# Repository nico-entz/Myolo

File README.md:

# Myolo

Myolo ist ein Partikel/Myonendetektor auf der Basis von Szintillatoren und Silizium-Photodioden, der ohne SMD-Bauteile aufgebaut werden kann.

Myolo nutzt Koinzidenz, um Myonen von anderen Teilchen zu unterscheiden. Um dies zu realisieren, nutzt er zwei voneinander unabhängige Detektoren. Anhand der zeitlichen Korrelation der Signale beider Detektoren kann auf die Teilchenart geschlossen werden.

Als Szintillatoren kommen Bicron BC408-Plastikszintillatoren der Maße 50x50x10 mm zum Einsatz.

Als SiPMs werden onsemi MICROFC-60035-SMT-TR genutzt. Die Bias-Spannung von 29,5 V wird mittels eines simplen DC-DC-Wandlers erzeugt.

Die für die Operationsverstärkerschaltung notwendige symmetrische Versorgungsspannung von +/- 15V wird ebenfalls durch einen DC-DC-Wandler erzeugt.

Myolo basiert lose auf dem CosmicWatch-Projekt (http://www.cosmicwatch.lns.mit.edu/) und nutzt daher auch dessen SiPM-PCB (https://github.com/spenceraxani/CosmicWatch-Desktop-Muon-Detector-v2/blob/master/PCB_Files/PCB_Gerber_files.zip).

Im Gegensatz zu CosmicWatch nutzt Myolo jedoch einen leistungsfähigen STM32H7-Mikrocontroller, wodurch es möglich wird, beide Detektoren quasi zeitgleich auszulesen.

--------------------------------------

Myolo is a particle/muon detector based on scintillators and silicon photodiodes that can be constructed without SMD components.

Myolo uses the coincidence method to distinguish muons from other particles. To achieve this, it uses two independent detectors. The type of particle can be determined based on the temporal correlation of the signals from both detectors.

Bicron BC408 plastic scintillators measuring 50x50x10 mm are used as scintillators.

Onsemi MICROFC-60035-SMT-TR are used as SiPMs. The bias voltage of 29.5 V is generated by a simple DC-DC converter. 

The symmetrical supply voltage of +/- 15V required for the operational amplifier circuit is also generated by a DC-DC converter.

Myolo is loosely based on the CosmicWatch project (http://www.cosmicwatch.lns.mit.edu/) and therefore also uses its SiPM PCB (https://github.com/spenceraxani/CosmicWatch-Desktop-Muon-Detector-v2/blob/master/PCB_Files/PCB_Gerber_files.zip).

Unlike CosmicWatch, however, Myolo uses a powerful STM32H7 microcontroller, which makes it possible to read out both detectors virtually simultaneously.

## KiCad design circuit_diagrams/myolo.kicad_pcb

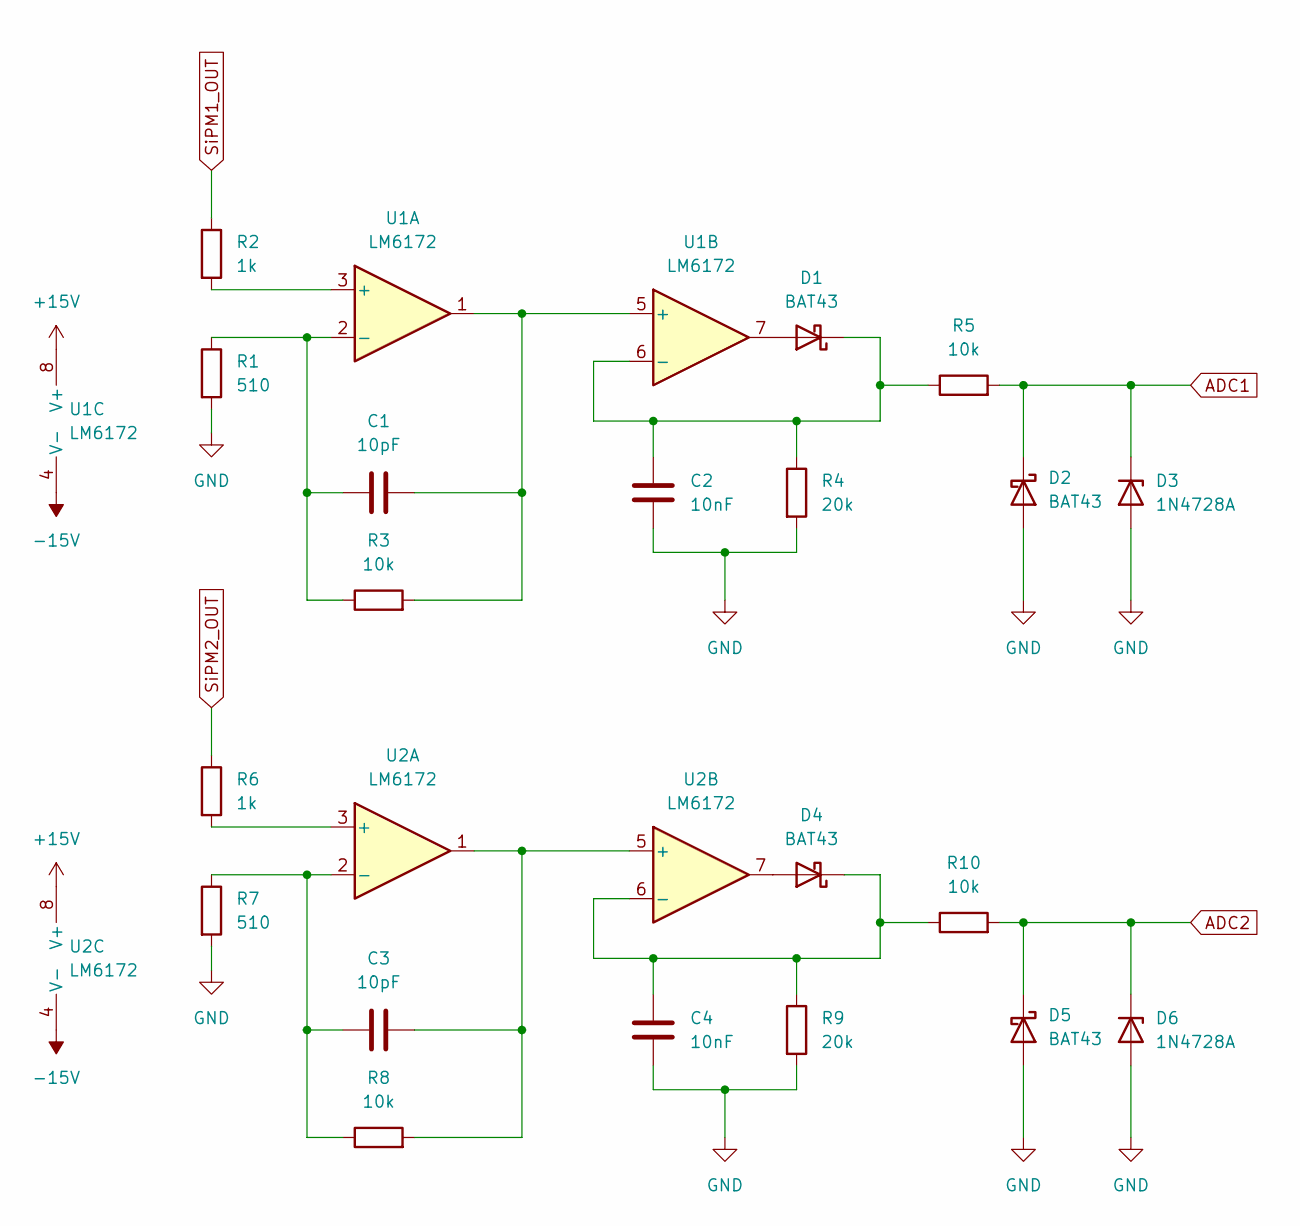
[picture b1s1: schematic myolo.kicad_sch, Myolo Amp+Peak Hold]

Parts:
C1, C3: 10pF; CP_Radial_D4.0mm_P2.00mm
C2, C4: 10nF; CP_Radial_D4.0mm_P2.00mm
D1, D2, D4, D5: BAT43; D_DO-35_SOD27_P7.62mm_Horizontal
D3, D6: 1N4728A; D_DO-41_SOD81_P10.16mm_Horizontal
R1, R7: 510; R_Axial_DIN0207_L6.3mm_D2.5mm_P15.24mm_Horizontal
R2, R6: 1k; R_Axial_DIN0207_L6.3mm_D2.5mm_P15.24mm_Horizontal
R3, R5, R8, R10: 10k; R_Axial_DIN0207_L6.3mm_D2.5mm_P15.24mm_Horizontal
R4, R9: 20k; R_Axial_DIN0207_L6.3mm_D2.5mm_P15.24mm_Horizontal
U1, U2: LM6172; DIP-8_W10.16mm

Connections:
+15V: U1.8 (V+), U2.8 (V+)
-15V: U1.4 (V-), U2.4 (V-)
ADC1: D2.1 (K), D3.1 (K), R5.2
ADC2: D5.1 (K), D6.1 (K), R10.2
GND: C2.2, C4.2, D2.2 (A), D3.2 (A), D5.2 (A), D6.2 (A), R1.2, R4.2, R7.2, R9.2
unnamed: D1.2 (A), U1.7
unnamed: C2.1, D1.1 (K), R4.1, R5.1, U1.6 (-)
unnamed: D4.2 (A), U2.7
unnamed: C4.1, D4.1 (K), R9.1, R10.1, U2.6 (-)
unnamed: R2.2, U1.3 (+)
unnamed: C1.1, R1.1, R3.1, U1.2 (-)
unnamed: C1.2, R3.2, U1.1, U1.5 (+)
unnamed: R6.2, U2.3 (+)
unnamed: C3.1, R7.1, R8.1, U2.2 (-)
unnamed: C3.2, R8.2, U2.1, U2.5 (+)
SiPM1_OUT: R2.1
SiPM2_OUT: R6.1

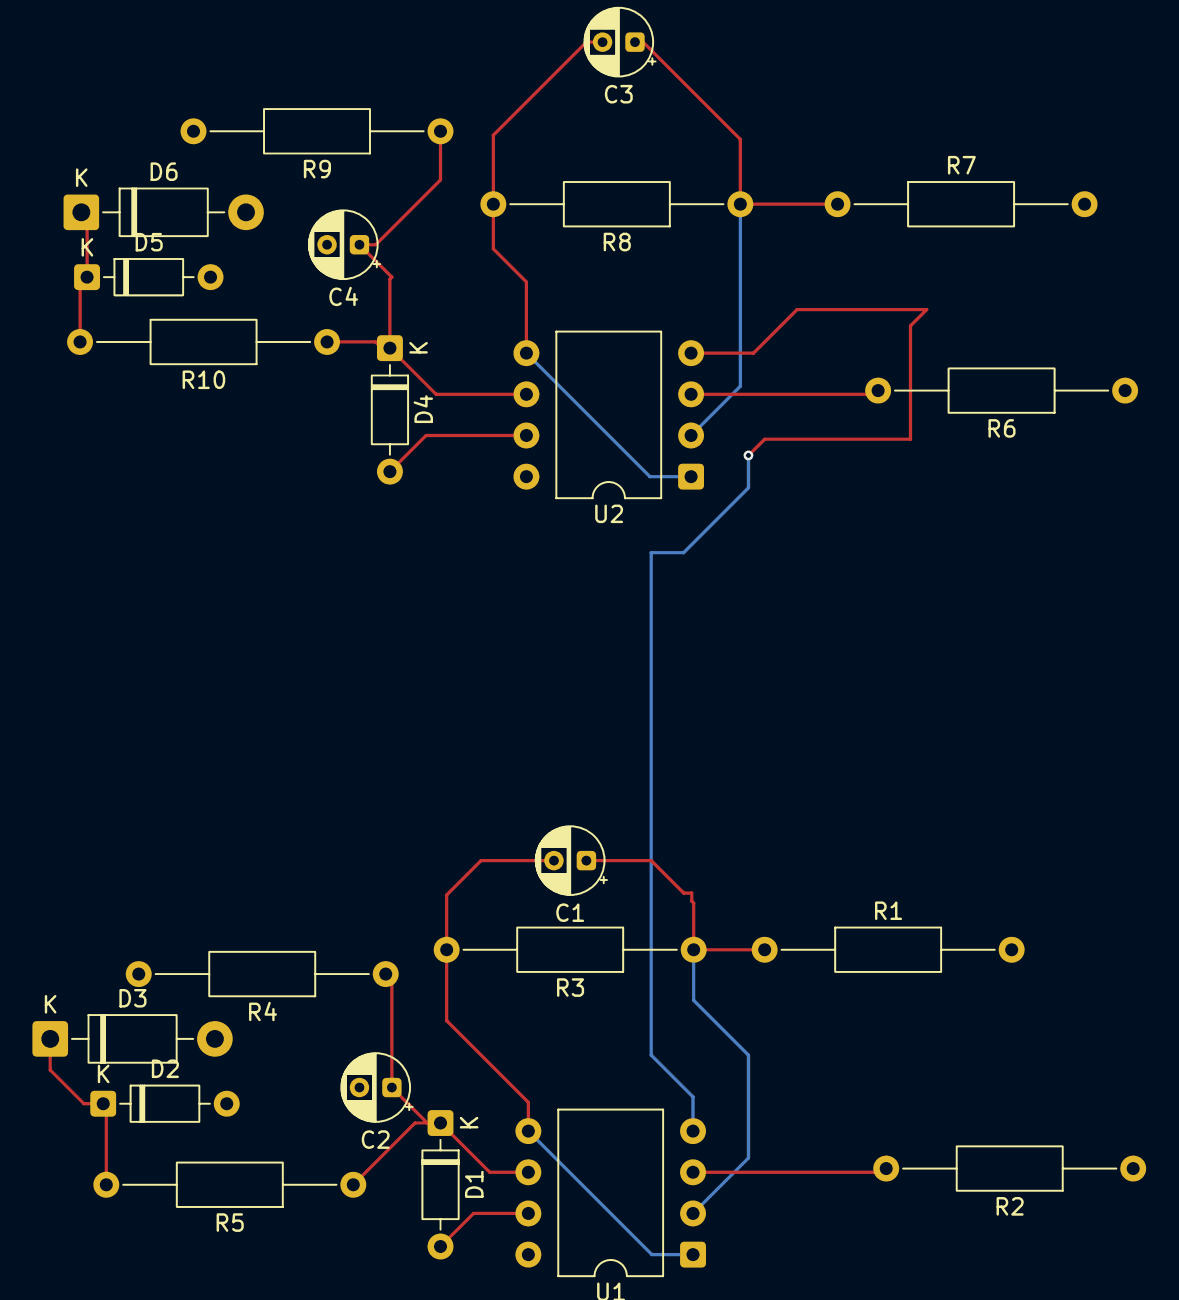
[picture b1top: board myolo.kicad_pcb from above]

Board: 2 copper layers, 22 parts (0 on the bottom side), 15 nets.

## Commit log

2025-10-02 added readme
2025-10-02 edited readme
